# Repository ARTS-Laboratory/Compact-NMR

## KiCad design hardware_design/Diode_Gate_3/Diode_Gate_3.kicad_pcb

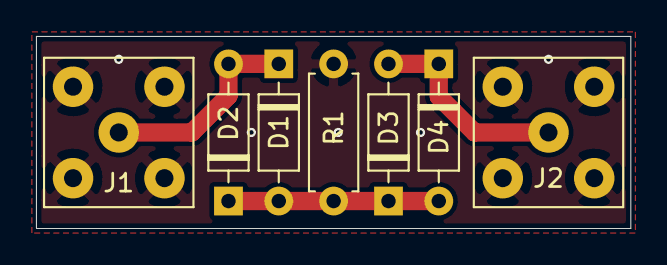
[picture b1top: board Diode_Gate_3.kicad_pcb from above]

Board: 2 copper layers, 33.0 x 10.7 mm, 7 parts (0 on the bottom side), 4 nets.

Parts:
D1, D2, D3, D4: 1N4148; D_DO-35_SOD27_P7.62mm_Horizontal
J1, J2: Conn_Coaxial; SMA_Amphenol_132203-12_Horizontal
R1: 10k; R_Axial_DIN0207_L6.3mm_D2.5mm_P7.62mm_Horizontal

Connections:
GND: J1.2, J2.2, R1.2
unnamed: D1.1, D2.2, J1.1
unnamed: D1.2, D2.1, D3.1, D4.2, R1.1
unnamed: D3.2, D4.1, J2.1
